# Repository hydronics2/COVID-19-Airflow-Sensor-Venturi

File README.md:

#### This sensor was abandoned because it was similar enough to another prototype using venturi type sensor based on a delta pressure reading. An ongoing airflow sensor project is here: [AFH55M12](https://github.com/hydronics2/COVID-19-Airflow-Sensor-AFH55M12) 

# Easy Flow Rate Sensor - venturi PCB

## Project Description ([from Helpful Engineering](https://www.helpfulengineering.org/))
The intent here is to create a monitoring device, based on a mass airflow meter, that can be used when splitting a ventilator into two or more patients. This will allow staff to monitor individual patients while being controlled by one device in extreme situations where the number of ventilators are not enough to handle the number of patients. The readout should be visible locally on the device and there may need to be parameters input by staff to create a safe operating range and to possibly create alarms when the system is measuring an out of range parameter.

### [Project Requirements](https://docs.google.com/document/d/17Ps910A2vRwnM4EM6F-71GNG1XNa0PaeImd53F7428c/edit?usp=sharing)

This version of the flow rate sensor PCB has off the shelf micro-controllers for quick prototyping. Developed through

The printed circuit board (PCB) accepts multiple Arduino platforms made by Adafruit including their line of [Adafruit Feather](https://www.adafruit.com/category/777) type micro-controllers and [Adafruit ItsyBitsy](https://www.adafruit.com/category/1008) micro-controllers.   The Adafruit feathers include wifi and SAMD M0 and M4 options. All the ItsyBitsy 3V models (M0, M4, and 32u4) should work fine.

[google Doc](https://docs.google.com/document/d/14zgp7OhsyWClFdLCb04ITVAHAoAawH8Gl29P4oe5PJs/edit?usp=sharing)

### Still to do
- select the operational amplifiers and gain serving the pressure sensors
- Select alarm conditions
- Might need to add a separate power connector (⅛” barrel?)  as the USB micro connector might not be strong enough
- Verify any i2C conflicts between humidity sensor and OLED display

### General Operation
.....

### Bill of Materials
- differential pressure sensor, MP3V5004DP,
- gauge pressure sensor, MP3V5004G
- humidity sensor through-hole - H1H800, digikey 480-5706-1-ND
- humidity sensor surface mount - SHTC3, digikey 1649-1100-1-ND
- piezo buzzer, generic, 6.5mm pitch
- transistor to drive piezo pn2222A
- oled display, generic 1306 OLED, 128 x 64 pixels
- Linear 3.3v regulator LDL1117S33R
- Rotary Encoder and momentary switch, Bourns PEC12R-4220F-S0012-ND
- generic 6mm user defined momentary tactile switch
- generic 1206 smd LEDs for Power, Error, and TBD LED indicator

### Pressure Sensors
Two pressure sensors used here. Both manufactured by [NXP MP3V5004 Series](https://www.nxp.com/docs/en/data-sheet/MP3V5004G.pdf)
- One pressure sensor measures differential pressure from an external venturi
- One pressure sensor measures gauge pressure.
Both pressure sensors are connected directly to the micro-controllers ADC inputs as well as operational amplifiers so their outputs may be amplified as needed. (A0, A1, A2, A3,A4,A5).

### Micro-Controller Pinout
#### Feather ESP32 Pinout
#### Not up to date

#### ItsyBitsy Pinout
#### Not up to date

### Power
Power is delivered through the USB cable on the micro-controller. The Feather micro-controllers have a lipo charge circuit.  The main board is powered from the vBat pin of the micro-controller. The smaller Adafruit micro-controller does not have a lipo charge circuit and powers the PCB from the USB pin.
Feather lipo charge circuit. A 3.3v linear regulator is the analog power supply to the pressure sensors and operational amplifiers. This is a generic 3.3V regulator: LDL1117S33R

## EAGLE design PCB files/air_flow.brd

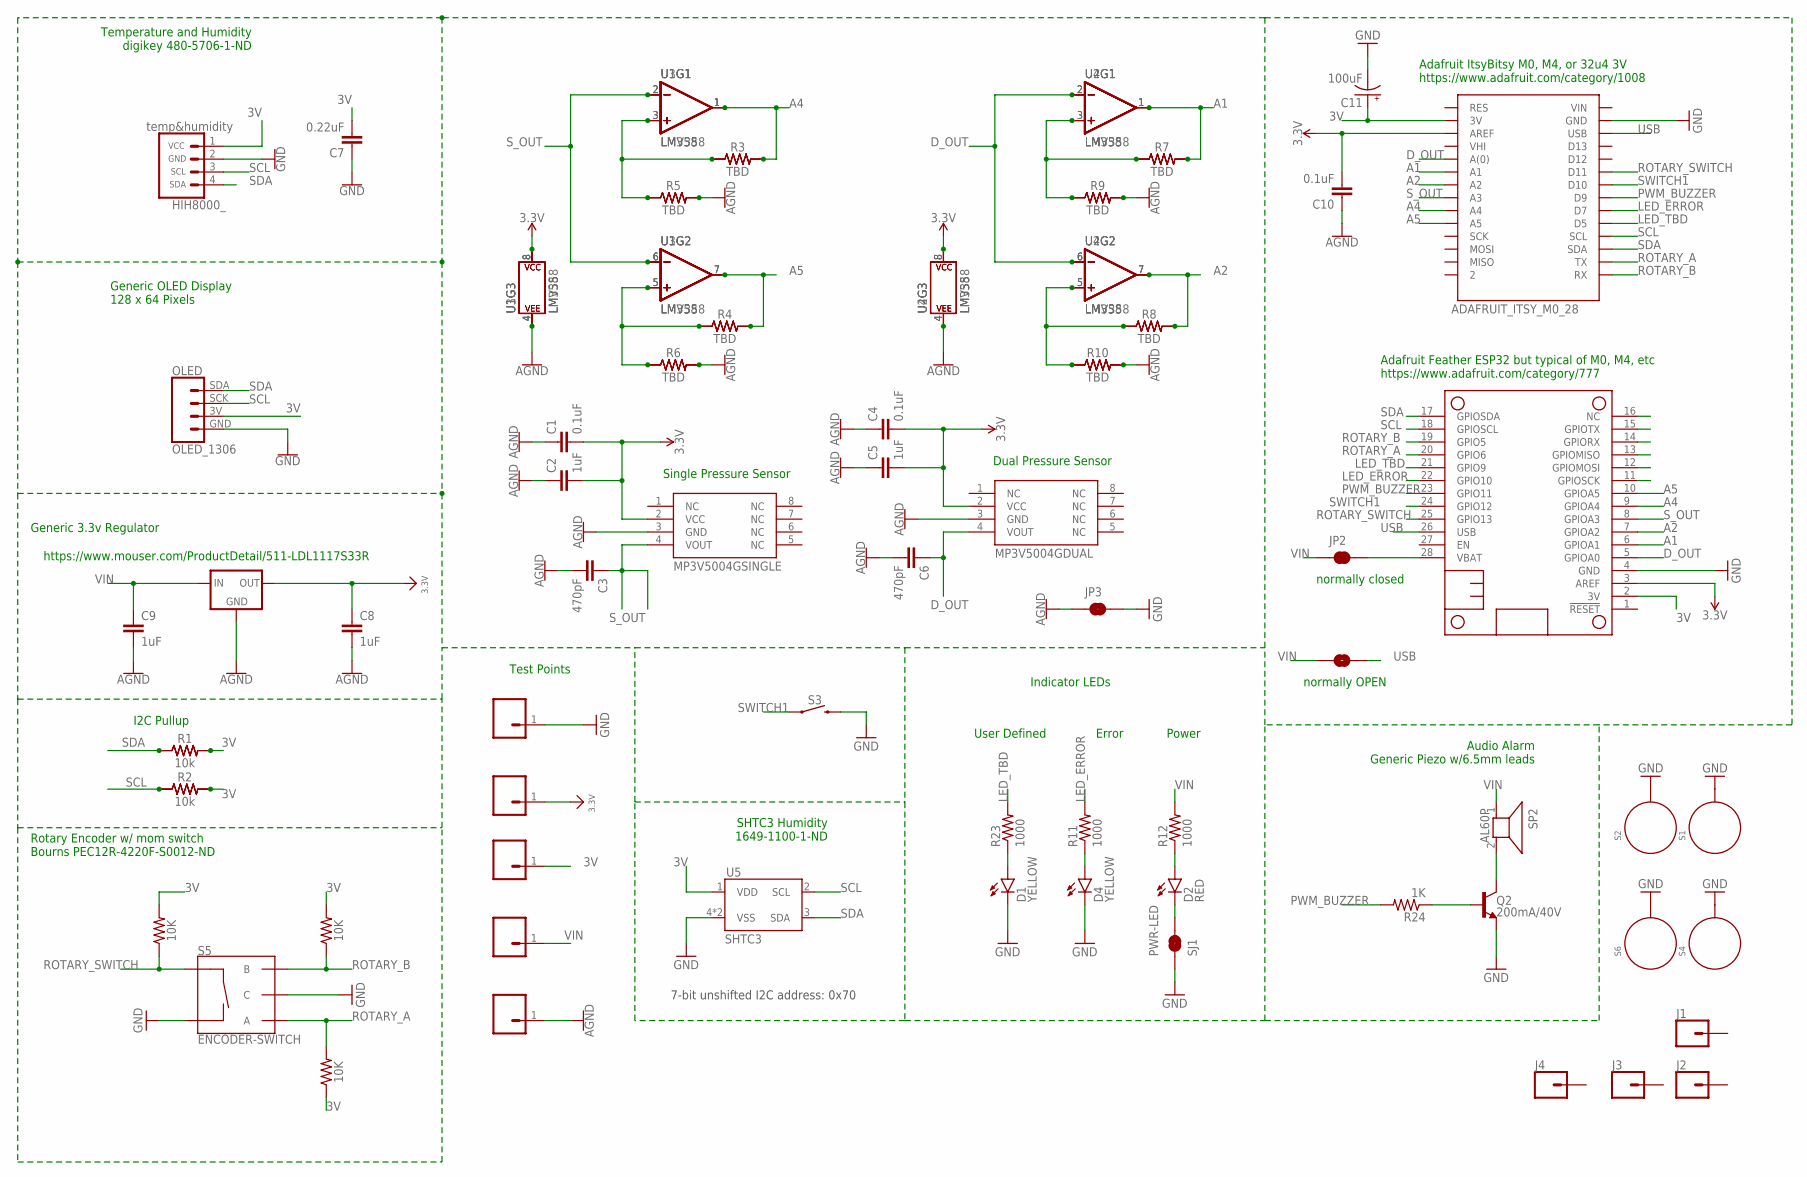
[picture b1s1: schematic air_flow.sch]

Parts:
3V_REGULATOR: LDL1117_5V_REG; SOT223
C1, C4, C10: 0.1uF; CAP-PTH-SMALL-KIT
C2, C5, C8, C9: 1uF; CAP-PTH-SMALL-KIT
C3, C6: 470pF; CAP-PTH-SMALL-KIT
C7: 0.22uF; CAP-PTH-SMALL-KIT
C11: 100uF; CPOL-RADIAL-2.5MM-6.5MM
D1, D4: YELLOW; LED-1206
D2: RED; LED-1206
J1, J2, J3, J4: CONN_01; 1X01
JP1: JUMPER-SMT_2_NO_NO-SILK; SMT-JUMPER_2_NO_NO-SILK
JP2, JP3: JUMPER-SMT_2_NC_TRACE_SILK; SMT-JUMPER_2_NC_TRACE_SILK
MS2: FEATHERWING_NODIM; FEATHERWING_DIM
Q2: 200mA/40V; TO-92
R1, R2: 10k; AXIAL-0.3
R3, R4, R5, R6, R7, R8, R9, R10: TBD; AXIAL-0.3
R11, R12, R23: 1000; 0805
R13, R14, R15, R16, R17, R18, R19, R20, R21, R22: 0.3; 0805
R24: 1K; 0805
R26, R27, R28: 10K; 0805
S1, S2, S4, S6: STANDOFF_ELECTRICAL5-32; STANDOFF_ELECTRICAL_5_32
S3: MOMENTARY-SWITCH-SPST-PTH-6.0MM-KIT; TACTILE_SWITCH_PTH_6.0MM_KIT
S5: ENCODER-SWITCH; ROTARY_ENC_PLAIN
SJ1: PWR-LED; PAD-JUMPER-2-NC_BY_TRACE_NO_SILK
SP2: AL60P
U1, U2: LM358; DIP08
U3, U4: LMV358; SO08
U5: SHTC3
U$1: OLED_1306
U$2: MP3V5004GSINGLE; MP3V5004GP
U$3: MP3V5004GDUAL; MP3V5004DP
U$4: HIH8000_; HIH8120_TH
U$20, U$26, U$31, U$39, U$40: CONN_0138MILL; 1X01-40MILL
U$45: ADAFRUIT_ITSY_M0_28; ADAFRUIT_ITS_MO_28

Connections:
3.3V: 3V_REGULATOR.2 (OUT), 3V_REGULATOR.4 (OUT), C1.2, C2.2, C4.2, C5.2, C8.1, C10.2, MS2.3 (AREF), U1.8 (P$V+), U2.8 (P$V+), U3.8 (P$V+), U4.8 (P$V+), U$2.2 (VCC), U$3.2 (VCC), U$39.1, U$45.AREF
3V: C7.2, C11.1 (+), MS2.2 (3V), R1.P$2 (2), R2.P$2 (2), R21.2, R22.2, R26.2, R27.1, R28.2, U5.1 (VDD), U$1.3V (VCC), U$4.1 (VCC), U$20.1, U$45.3V
A1: MS2.6 (GPIOA1), R7.P$2 (2), R17.2, U2.1 (OUT), U4.1 (OUT), U$45.A1
A2: MS2.7 (GPIOA2), R8.P$2 (2), R19.2, U2.7 (OUT), U4.7 (OUT), U$45.A2
A4: MS2.9 (GPIOA4), R3.P$2 (2), R16.2, U1.1 (OUT), U3.1 (OUT), U$45.A4
A5: MS2.10 (GPIOA5), R4.P$2 (2), R14.2, U1.7 (OUT), U3.7 (OUT), U$45.A5
AGND: 3V_REGULATOR.1 (GND), C1.1, C2.1, C3.2, C4.1, C5.1, C6.2, C8.2, C9.2, C10.1, JP3.1, R5.P$2 (2), R6.P$2 (2), R9.P$2 (2), R10.P$2 (2), R13.2, R15.2, R18.2, R20.2, U1.4 (P$V-), U2.4 (P$V-), U3.4 (P$V-), U4.4 (P$V-), U$2.3 (GND), U$3.3 (GND), U$26.1
D_OUT: C6.1, MS2.5 (GPIOA0), U2.2 (-IN), U2.6 (-IN), U4.2 (-IN), U4.6 (-IN), U$3.4 (VOUT), U$45.A0 (A(0))
GND: C7.1, C11.2 (-), D1.C, D4.C, JP3.2, MS2.4 (GND), Q2.1 (E), S1.P1, S2.P1, S3.3 (2), S4.P1, S5.C, S5.SW-, S6.P1, SJ1.1, U5.4 (VSS), U5.5 (VSS), U$1.GND, U$4.2 (GND), U$31.1, U$45.GND
LED_ERROR: MS2.22 (GPIO10), R11.2, U$45.D7
LED_TBD: MS2.21 (GPIO9), R23.2, U$45.D5
unnamed: R3.P$1 (1), R5.P$1 (1), R13.1, R16.1, U1.3 (+IN), U3.3 (+IN)
unnamed: D2.A, R12.1
unnamed: D1.A, R23.1
unnamed: R4.P$1 (1), R6.P$1 (1), R14.1, R15.1, U1.5 (+IN), U3.5 (+IN)
unnamed: R7.P$1 (1), R9.P$1 (1), R17.1, R18.1, U2.3 (+IN), U4.3 (+IN)
unnamed: R8.P$1 (1), R10.P$1 (1), R19.1, R20.1, U2.5 (+IN), U4.5 (+IN)
unnamed: Q2.3 (C), SP2.2
unnamed: Q2.2 (B), R24.1
unnamed: D4.A, R11.1
unnamed: D2.C, SJ1.2
PWM_BUZZER: MS2.23 (GPIO11), R24.2, U$45.D9
ROTARY_A: MS2.20 (GPIO6), R27.2, S5.A, U$45.TX
ROTARY_B: MS2.19 (GPIO5), R26.1, S5.B, U$45.RX
ROTARY_SWITCH: MS2.25 (GPIO13), R28.1, S5.SW+, U$45.D11
SCL: MS2.18 (GPIOSCL), R2.P$1 (1), R22.1, U5.2 (SCL), U$1.SCK, U$4.3 (SCL), U$45.SCL
SDA: MS2.17 (GPIOSDA), R1.P$1 (1), R21.1, U5.3 (SDA), U$1.SDA, U$4.4 (SDA), U$45.SDA
SWITCH1: MS2.24 (GPIO12), S3.1, U$45.D10
S_OUT: C3.1, MS2.8 (GPIOA3), U1.2 (-IN), U1.6 (-IN), U3.2 (-IN), U3.6 (-IN), U$2.4 (VOUT), U$45.A3
USB: JP1.2, MS2.26 (USB), U$45.USB
VBAT: JP2.2, MS2.28 (VBAT)
VIN: 3V_REGULATOR.3 (IN), C9.1, JP1.1, JP2.1, R12.2, SP2.1, U$40.1

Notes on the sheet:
I2C Pullup
Dual Pressure Sensor
Single Pressure Sensor
Temperature and Humidity digikey 480-5706-1-ND
Generic OLED Display 128 x 64 Pixels
normally closed
normally OPEN
Adafruit ItsyBitsy M0, M4, or 32u4 3V https://www.adafruit.com/category/1008
Adafruit Feather ESP32 but typical of M0, M4, etc https://www.adafruit.com/category/777
Generic 3.3v Regulator
Test Points
Indicator LEDs
Power
Error
User Defined
https://www.mouser.com/ProductDetail/511-LDL1117S33R
Audio Alarm Generic Piezo w/6.5mm leads
Rotary Encoder w/ mom switch Bourns PEC12R-4220F-S0012-ND
7-bit unshifted I2C address: 0x70
SHTC3 Humidity 1649-1100-1-ND

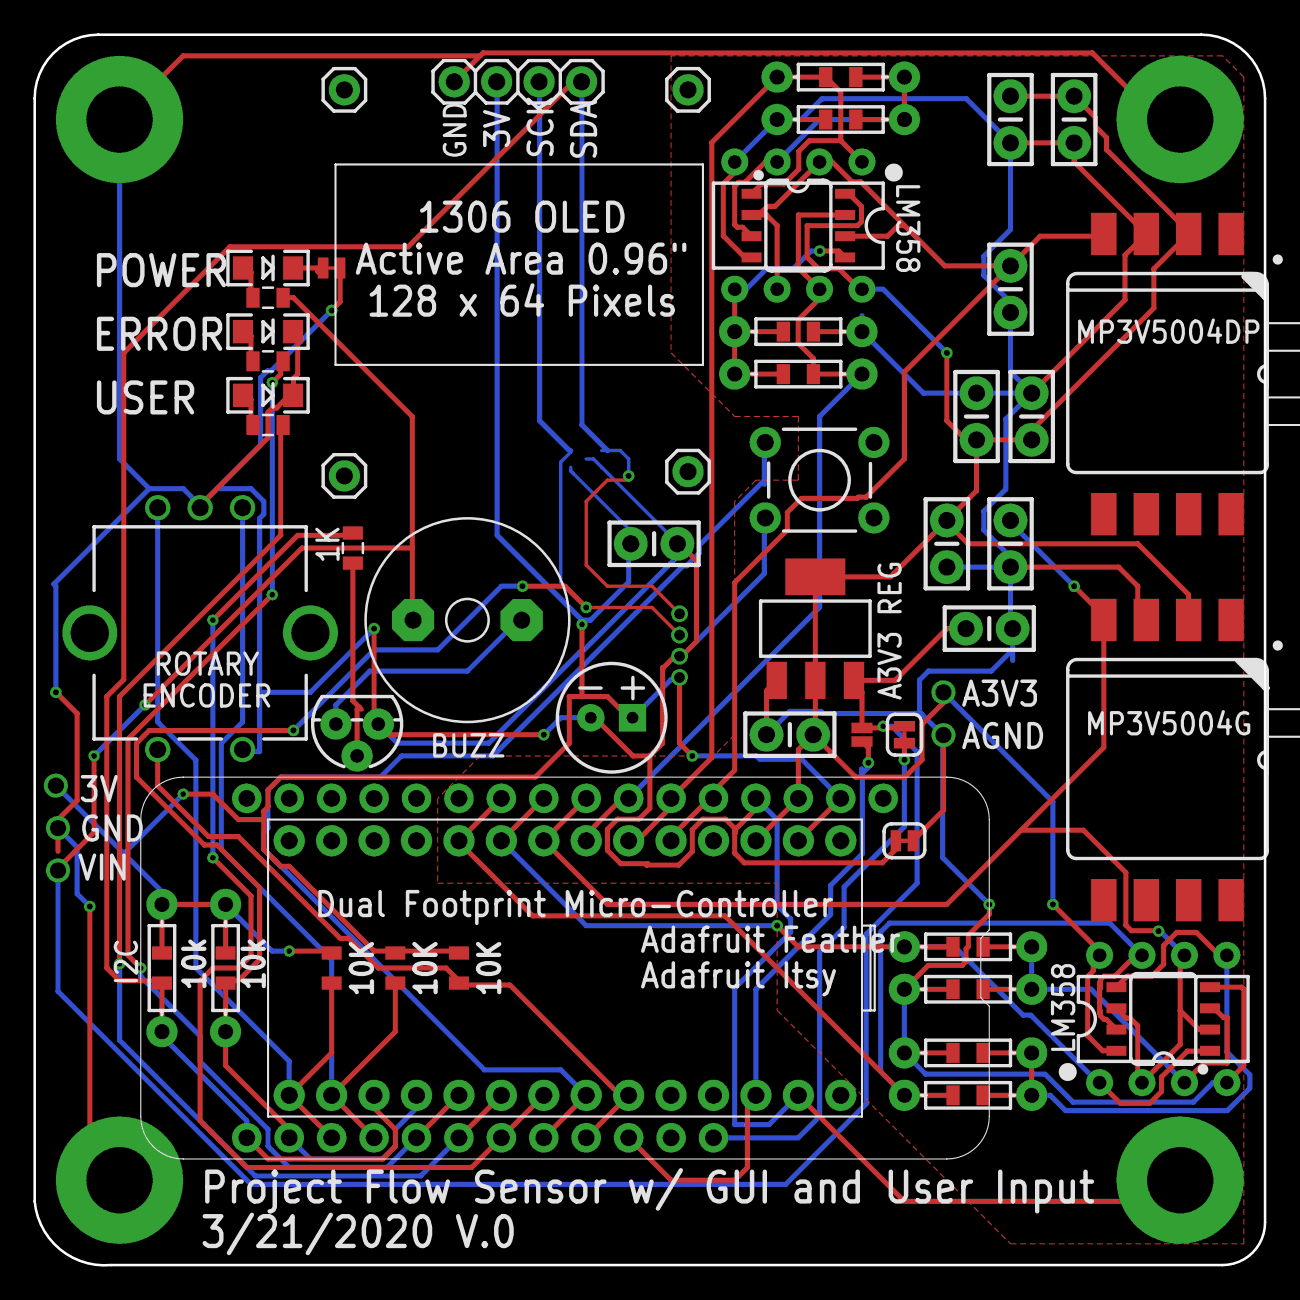
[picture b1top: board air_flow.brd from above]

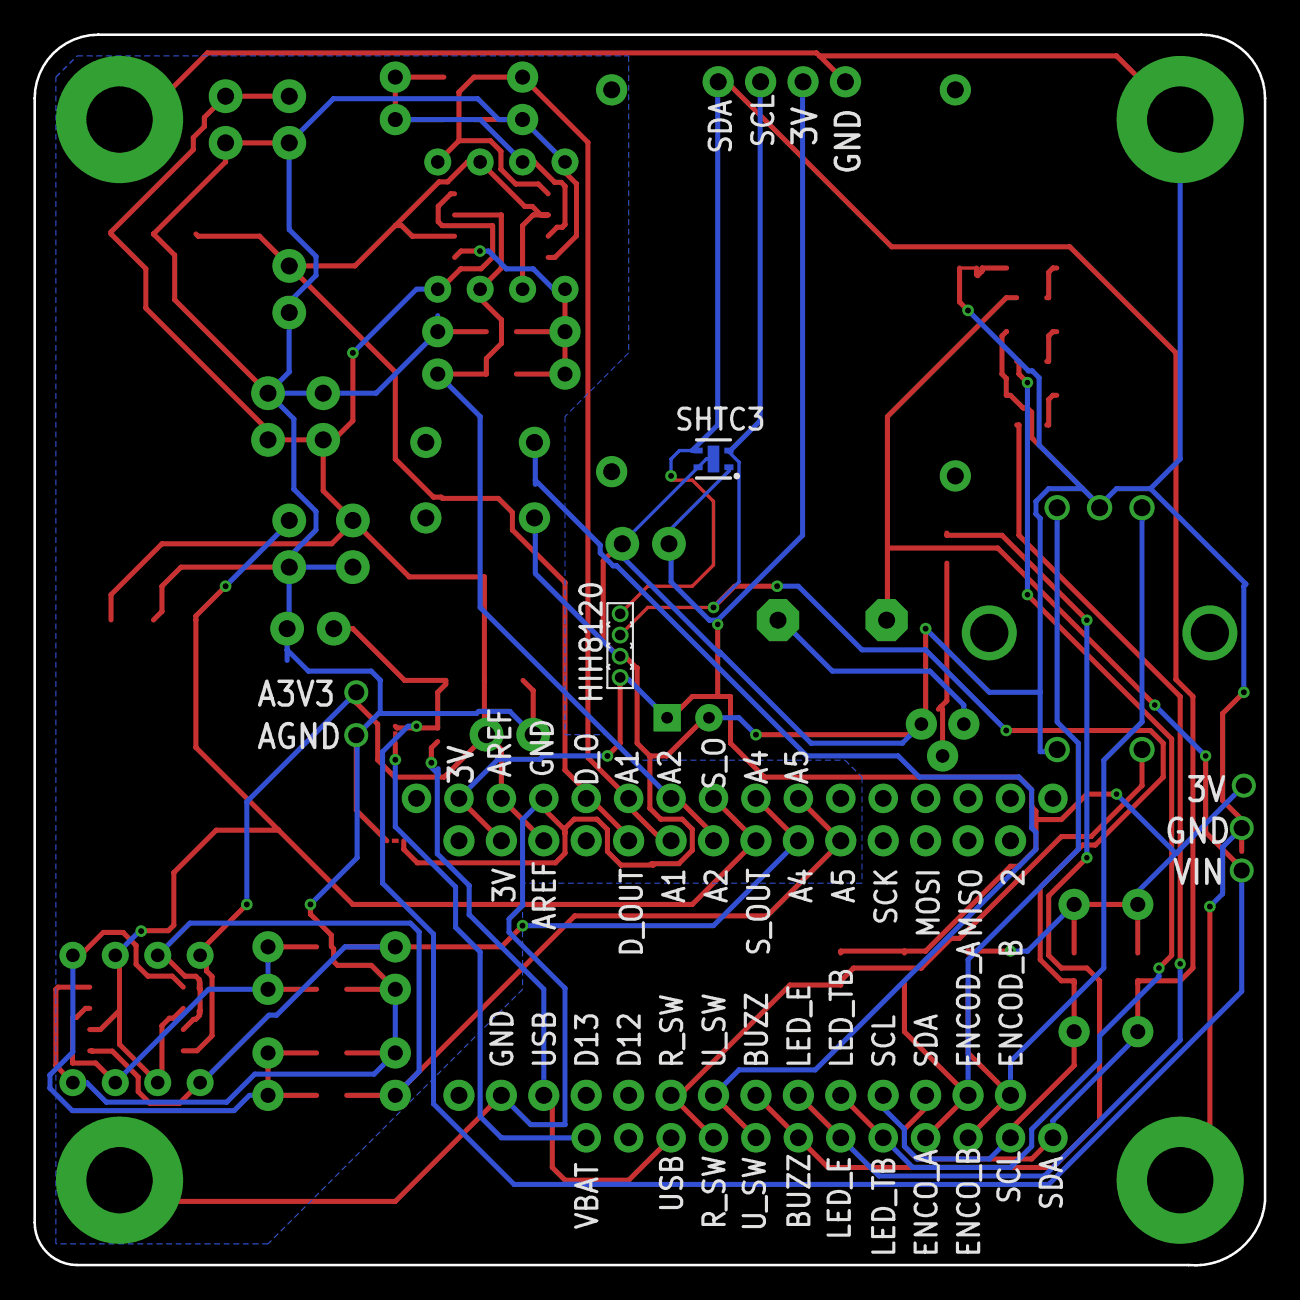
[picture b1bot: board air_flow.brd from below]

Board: 2 copper layers, 73.7 x 73.7 mm, 74 parts (2 on the bottom side), 32 nets.

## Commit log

2020-03-21 add pics
2020-03-21 add pic
2020-03-21 eagle files
2020-03-21 added eagle files
2020-03-22 update eagle files
2020-03-22 deleted stuff
2020-03-22 updated ealge v0 to JLCPCB
2020-03-22 added pic
2020-03-22 added kicad step file
2020-03-22 udpate
2020-04-05 Create air_flow.s##

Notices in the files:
parts and their libraries:
SparkFun-Capacitors: Licensing: Creative Commons ShareAlike 4.0 International - https://creativecommons.org/licenses/by-sa/4.0
microbuilder: This work is placed in the public domain, and may be freely used for commercial and non-commercial work with the following conditions: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
